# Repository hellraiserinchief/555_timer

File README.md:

# 555_timer
How to design a simple stable 555 timer circuit on KiCad and perpare it for milling using Cylone PCB milling machine

I referred to this webpage to create the circuit : https://www.electronics-tutorials.ws/waveforms/555_timer.html

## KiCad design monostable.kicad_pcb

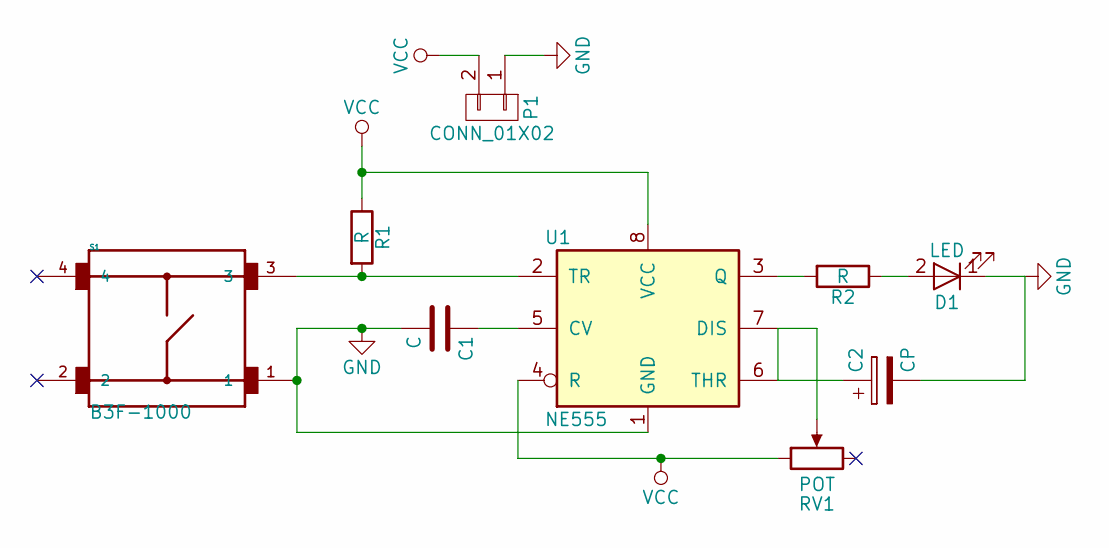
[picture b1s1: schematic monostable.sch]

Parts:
C1: C; C_Disc_D3_P2.5
C2: CP; C_Radial_D5_L6_P2.5
D1: LED; LED-5MM
P1: CONN_01X02; Pin_Header_Straight_1x02
R1, R2: R; Resistor_Horizontal_RM10mm
RV1: POT; Potentiometer_Triwood_RM-065
S1: B3F-1000; SW_B3F-1000
U1: NE555; DIP-8_W7.62mm_LongPads

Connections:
GND: C1.2, C2.2, D1.1 (K), P1.1, S1.1, U1.1 (GND)
unnamed: C1.1, U1.5 (CV)
unnamed: C2.1, RV1.2, U1.6 (THR), U1.7 (DIS)
unnamed: D1.2 (A), R2.1
unnamed: R1.2, S1.3, U1.2 (TR)
unnamed: R2.2, U1.3 (Q)
VCC: P1.2, R1.1, RV1.1, U1.4 (R), U1.8 (VCC)

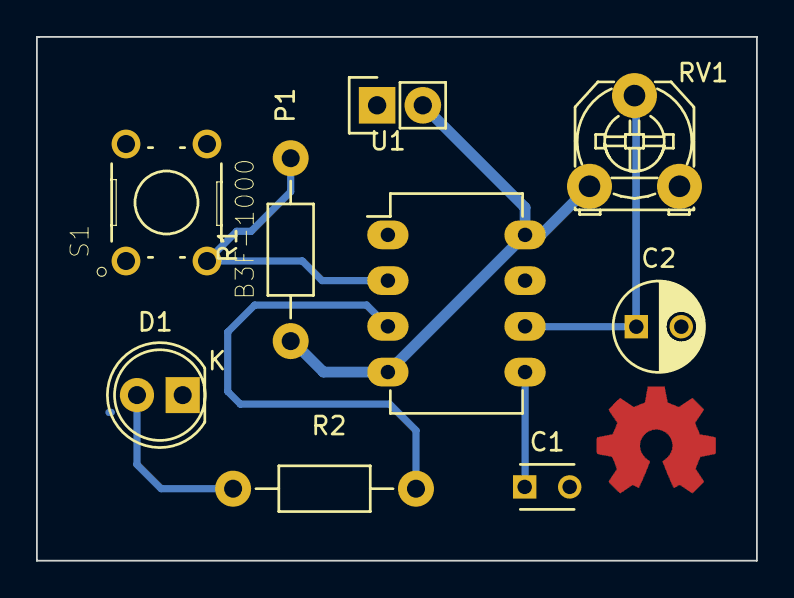
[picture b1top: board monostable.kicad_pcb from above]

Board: 2 copper layers, 40.0 x 29.1 mm, 9 parts (0 on the bottom side), 7 nets.

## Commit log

2018-08-08 add URL
